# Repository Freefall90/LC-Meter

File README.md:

# LC-Meter
Hardware design files for an inductance and capacitance meter

The STLs are exports from the STEP file. The other folders contain STEP files for the external components (a switch and the LCD).

There's also a very unfinished plated through hole version of the board (the PTH variant). I started on that before I figured out the problem with the weird oscillations and never finished it since the SMD board works fine with the added cap. 

# Attributions
The circuit design and firmware are courtesy of Phil Rice (VK3BHR) at https://sites.google.com/site/vk3bhr/home/index2-html

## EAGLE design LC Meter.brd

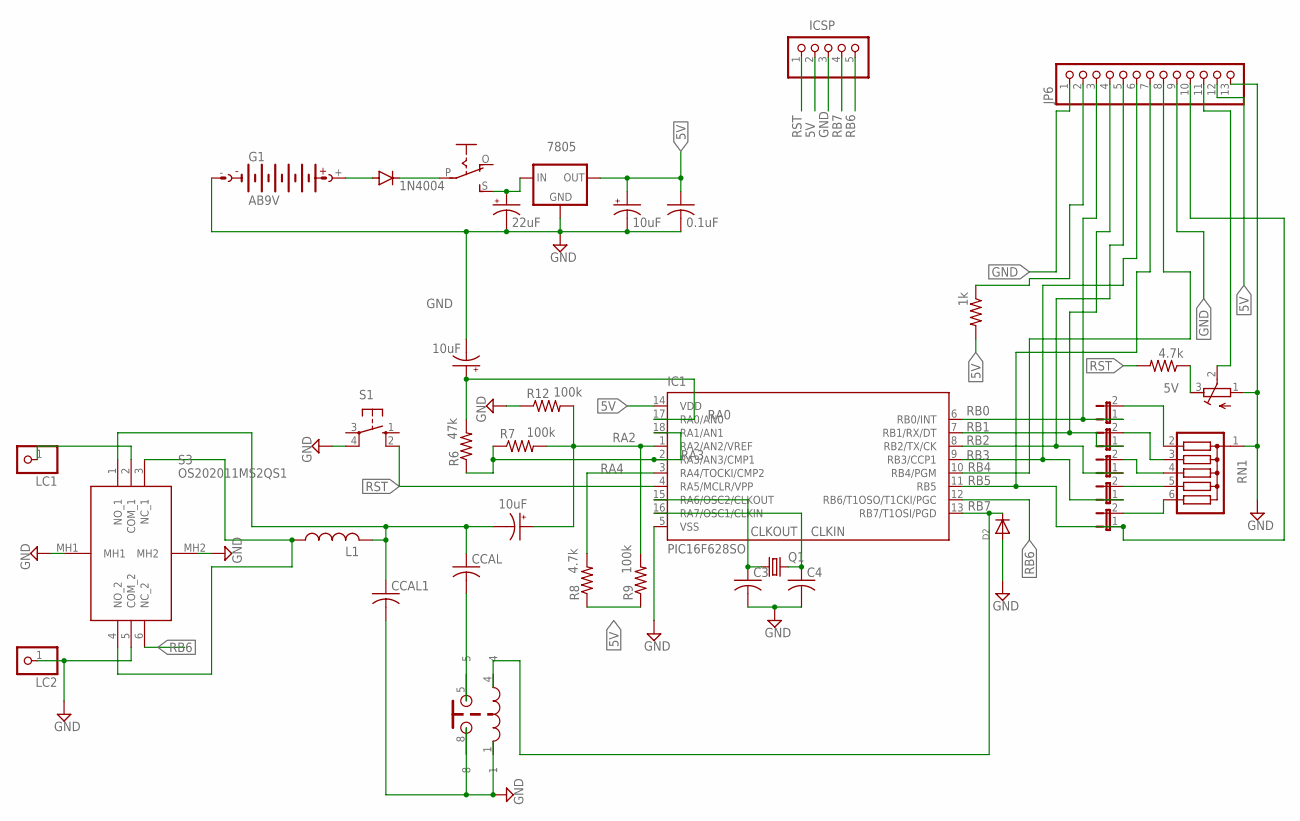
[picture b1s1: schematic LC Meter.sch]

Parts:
C1: 22uF; B/3528-21R
C2: 0.1uF; C0603
C3, C4: C-USC0603; C0603
C5, C6, C7: 10uF; E2-4
CCAL, CCAL1: C-US050-035X075; C050-035X075
D1: 1N4004; DO41-10
D2: DIODEDO-1N4148; DO-1N4148
G1: AB9V
IC1: PIC16F628SO; SO-18W
ICSP: PINHD-1X5; 1X05
JP1, JP2, JP3, JP4, JP5: JP1E; JP1
JP6: PINHD-1X13; 1X13
L1: L-US0207/12; 0207/12
LC1, LC2: PINHD-1X1; 1X01
Q1: CRYSTALHC49S; HC49/S
R1: 1k; R0603
R6: 47k; 0204/7
R7, R9, R12: 100k; 0204/7
R8, R10: 4.7k; 0204/7
R11: R-TRIMM3339P; RTRIM3339P
REED: REEDRELAY; COTO2204
RN1: G05R; SIL6
S1: 10-XX; B3F-10XX
S2: EG1218S; EG1218
S3: OS202011MS2QS1
VREG: 7805; 78XXS

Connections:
5V: C2.1, C6.+, IC1.14 (VDD), ICSP.2, JP6.12, R1.2, R8.1, R9.1, R10.1, R11.3 (E), VREG.OUT
CLKIN: C4.1, IC1.16 (RA7/OSC1/CLKIN), Q1.2
CLKOUT: C3.1, IC1.15 (RA6/OSC2/CLKOUT), Q1.1
GND: C1.-, C2.2, C3.2, C4.2, C6.-, C7.-, CCAL1.2, D2.A, G1.-, IC1.5 (VSS), ICSP.3, JP6.1, JP6.9, JP6.13, LC2.1, R11.1 (A), R12.1, REED.1, REED.8, RN1.1, S1.4 (P1), S3.5 (COM_2), S3.MH1, S3.MH2, VREG.GND
unnamed: JP5.2, RN1.6
unnamed: CCAL.2, REED.5
unnamed: C1.+, S2.S, VREG.IN
unnamed: D1.C, S2.P
unnamed: D1.A, G1.+
unnamed: C5.-, CCAL.1, CCAL1.1, L1.2, S3.1 (NO_1)
unnamed: JP4.2, RN1.5
unnamed: JP3.2, RN1.4
unnamed: JP2.2, RN1.3
unnamed: JP1.2, RN1.2
unnamed: LC1.1, S3.2 (COM_1)
unnamed: L1.1, S3.3 (NC_1), S3.4 (NO_2)
unnamed: JP6.11, R11.2 (S)
unnamed: JP6.2, R1.1
RA0: C7.+, IC1.17 (RA0/AN0), R6.2
RA2: C5.+, IC1.1 (RA2/AN2/VREF), R7.2, R9.2, R12.2; also elsewhere on the board
RA3: IC1.2 (RA3/AN3/CMP1), IC1.18 (RA1/AN1), R6.1, R7.1; also elsewhere on the board
RA4: IC1.3 (RA4/TOCKI/CMP2), R8.2
RB0: IC1.6 (RB0/INT), JP1.1, JP6.3
RB1: IC1.7 (RB1/RX/DT), JP2.1, JP6.4
RB2: IC1.8 (RB2/TX/CK), JP3.1, JP6.5
RB3: IC1.9 (RB3/CCP1), JP4.1, JP6.6
RB4: IC1.10 (RB4/PGM), JP6.8
RB5: IC1.11 (RB5), JP5.1, JP6.7, JP6.10
RB6: IC1.12 (RB6/T1OSO/T1CKI/PGC), ICSP.5, S3.6 (NC_2)
RB7: D2.C, IC1.13 (RB7/T1OSI/PGD), ICSP.4, REED.4
RST: IC1.4 (RA5/MCLR/VPP), ICSP.1, R10.2, S1.2 (S1)

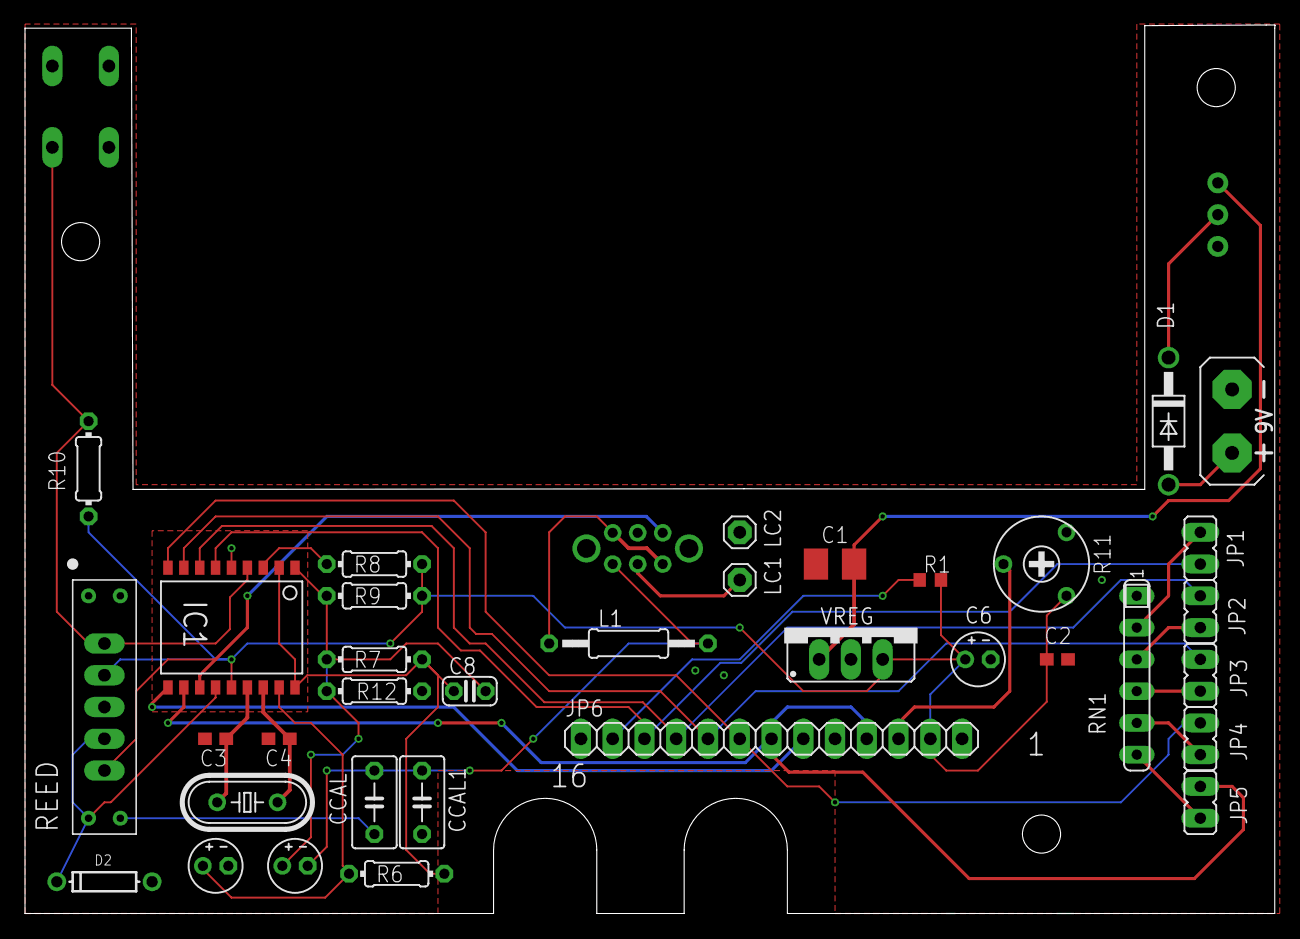
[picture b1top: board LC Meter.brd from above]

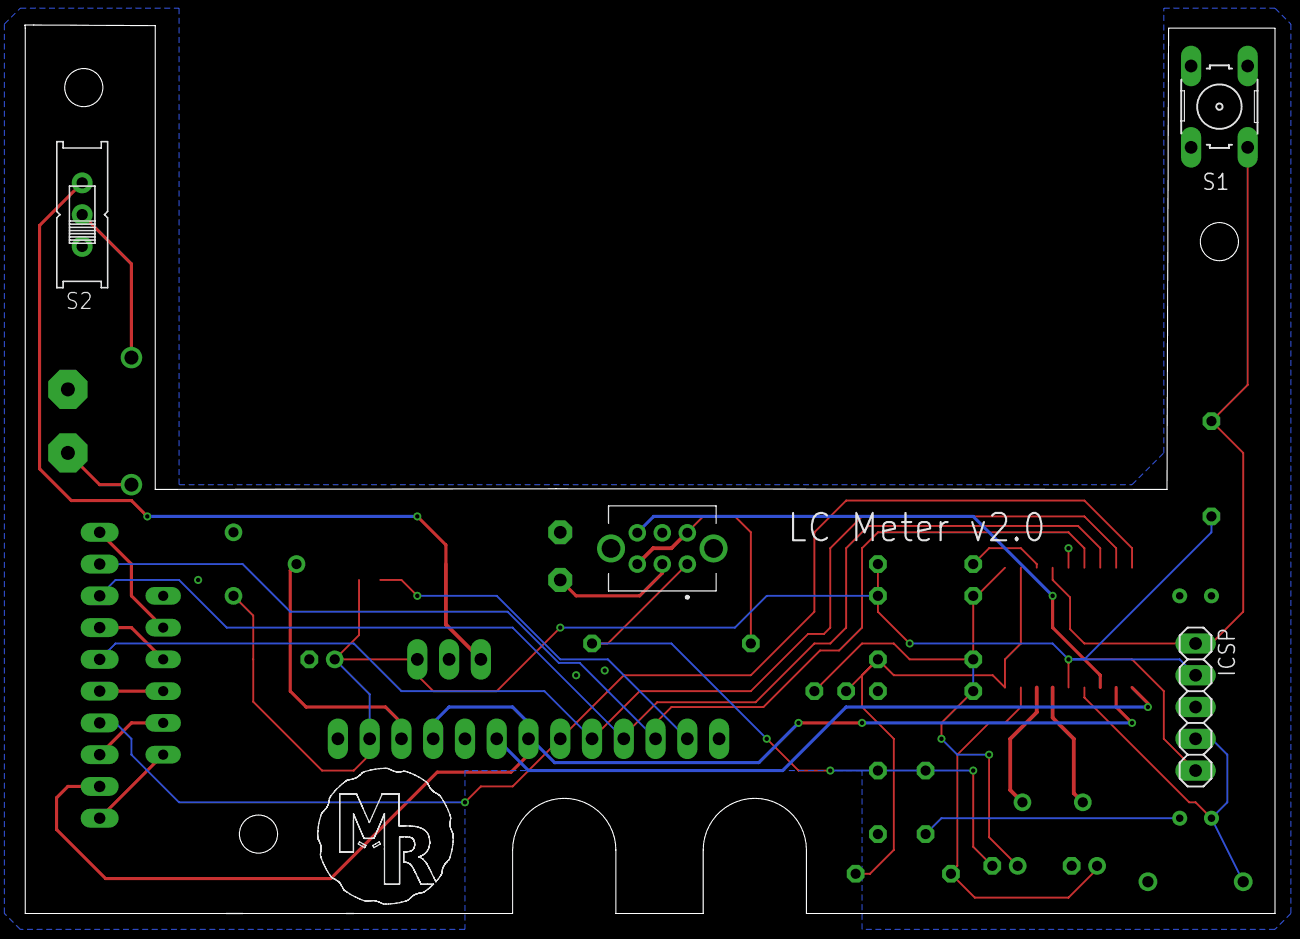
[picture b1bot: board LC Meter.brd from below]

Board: 2 copper layers, 99.9 x 71.0 mm, 39 parts (4 on the bottom side), 31 nets.

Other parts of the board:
C8: 10pF; C025-024X044

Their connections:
RA2: C8.2; also elsewhere on the board
RA3: C8.1; also elsewhere on the board

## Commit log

2021-08-07 Moved STLs
2021-08-07 Uploaded FW
2021-08-08 Fix for iCloud symlink issue
